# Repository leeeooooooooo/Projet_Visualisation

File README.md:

ce dossier contient l’api flask permettant de gérer les échanges entre la base de données et l’interface web, incluant l’authentification, la récupération des consommations et la gestion des seuils.

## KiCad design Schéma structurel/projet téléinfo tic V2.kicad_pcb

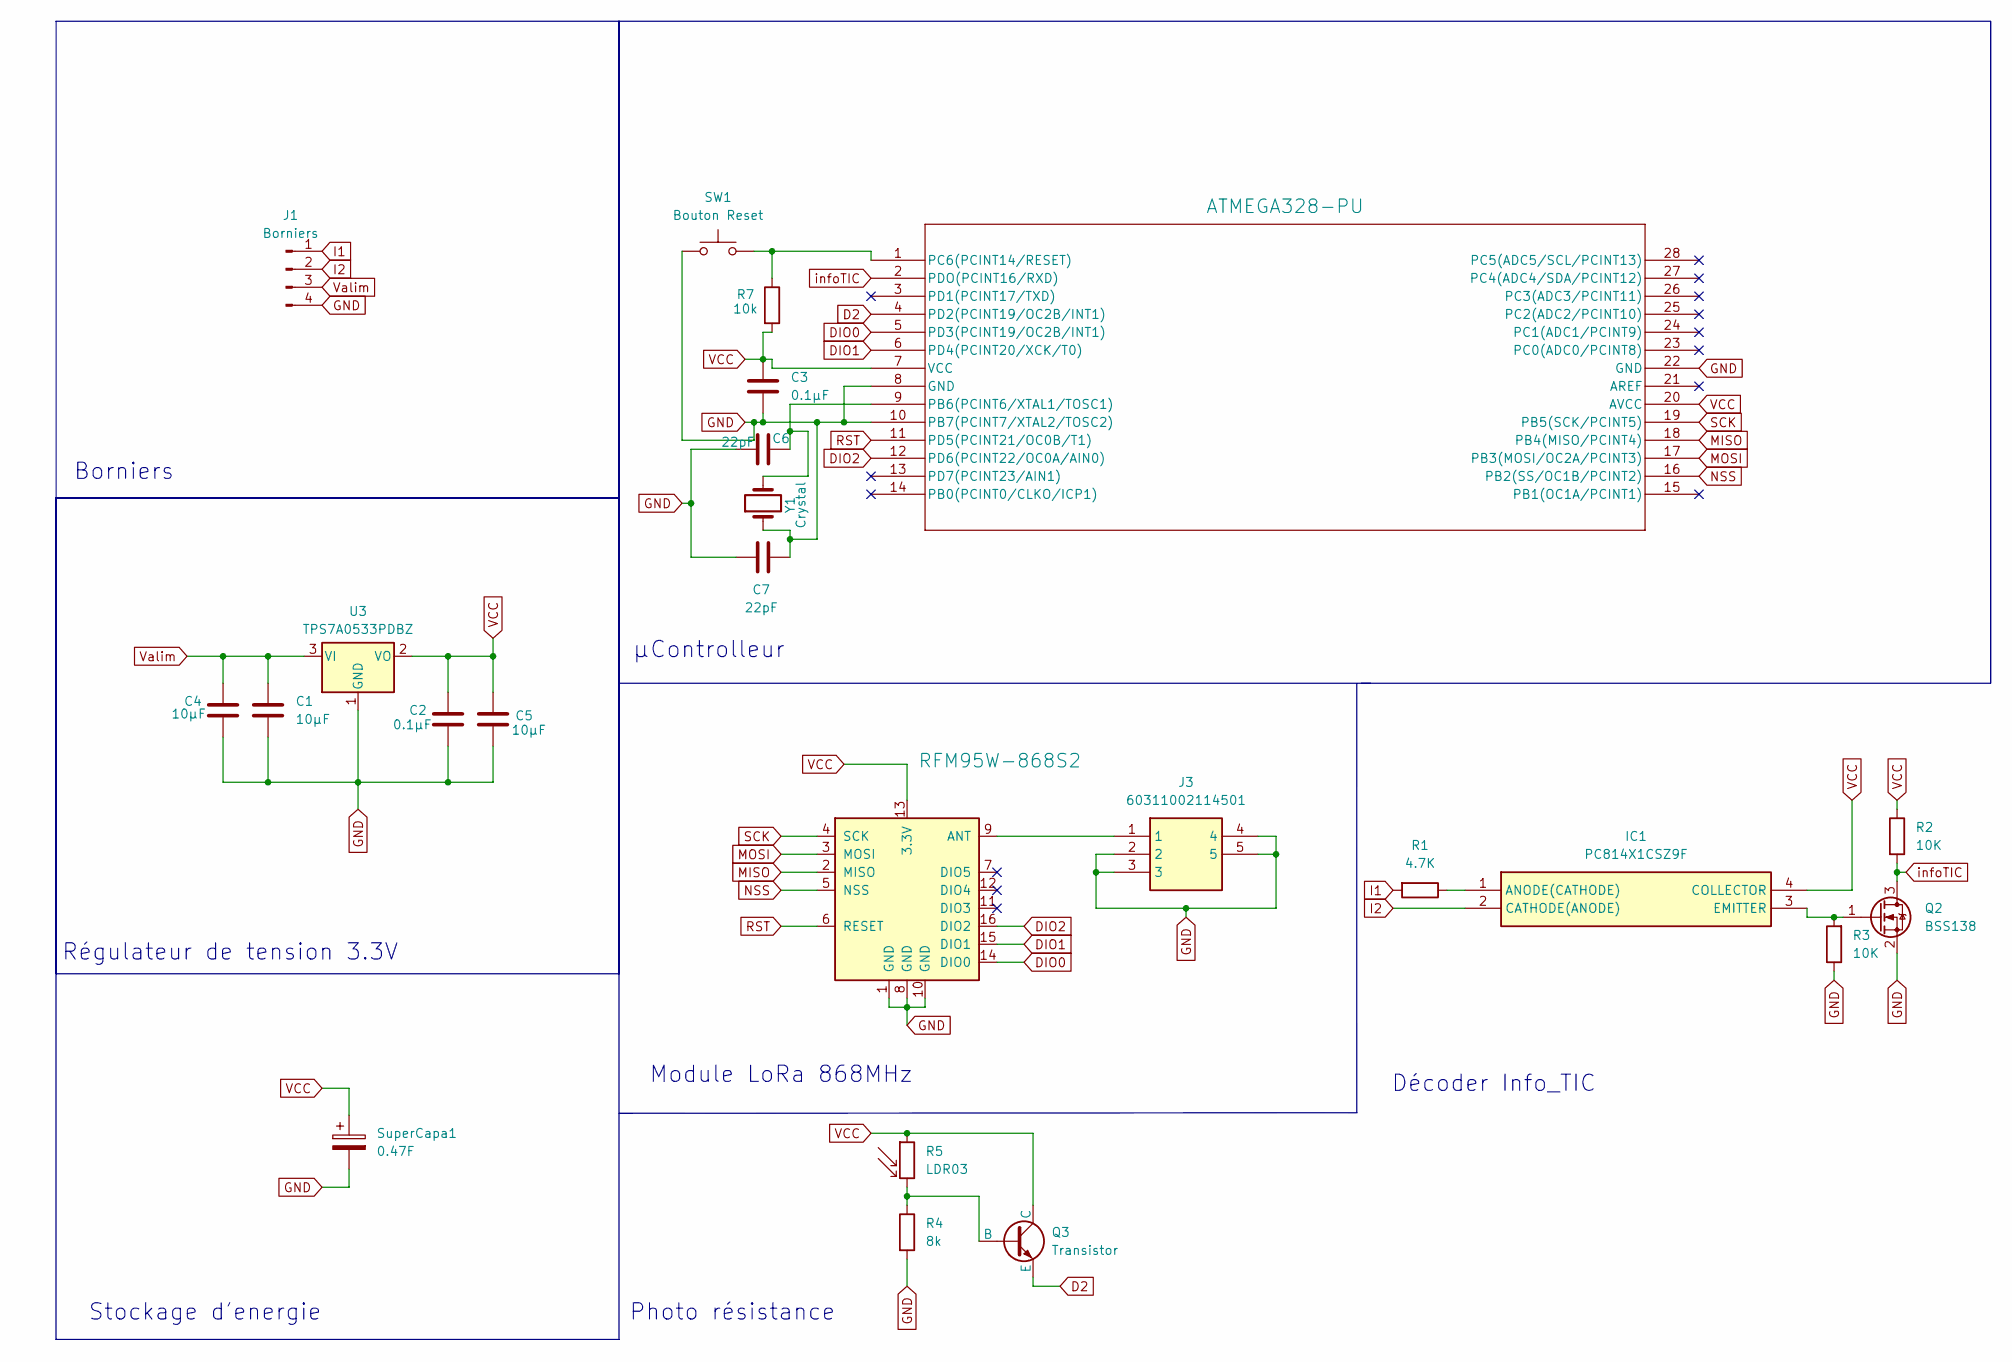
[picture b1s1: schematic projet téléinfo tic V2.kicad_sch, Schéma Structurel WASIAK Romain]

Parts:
C1, C4, C5: 10µF; CAPC3216X180N
C2, C3: 0.1µF; CAPC3216X180N
C6, C7: 22pF; CAPC3216X180N
IC1: PC814X1CSZ9F; DIP762W60P254L460H450Q4N; Manufacturer_Part_Number PC814X1CSZ9F; Mouser Part Number 852-PC814X1CSZ9F
J1: Borniers; 7966834
J3: 60311002114501; Manufacturer_Part_Number 60311002114501; Mouser Part Number 710-60311002114501
Q2: BSS138; SOT95P240X120-3N
Q3: Transistor; 2N2222A
R1: 4.7K; RESC3116X70N
R2, R3: 10K; RESC3216X74N
R4: 8k; ERJ8ENF1000V
R5: LDR03; PDVP8103
R7: 10k; RESC3216X74N
SW1: Bouton Reset; B3FS1012P
SuperCapa1: 0.47F; SCMQ14C474MRBA0
U2: RFM95W-868S2; XCVR_RFM95W-868S2
U3: TPS7A0533PDBZ; SOT95P237X112-3N
U4: ATMEGA328-PU; DIP1016W53P254L3468H457Q28N
Y1: Crystal; 830055663

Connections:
D2: Q3.3 (E), U4.4 (PD2(PCINT19/OC2B/INT1))
DIO0: U2.14 (DIO0), U4.5 (PD3(PCINT19/OC2B/INT1))
DIO1: U2.15 (DIO1), U4.6 (PD4(PCINT20/XCK/T0))
DIO2: U2.16 (DIO2), U4.12 (PD6(PCINT22/OC0A/AIN0))
GND: C1.2, C2.2, C3.2, C4.2, C5.2, C6.1, C7.1, C7.2, J1.4, J3.2, J3.3, J3.4, J3.5, Q2.2 (S), R3.1, R4.2, SW1.1, SuperCapa1.2, U2.1 (GND), U2.8 (GND), U2.10 (GND), U3.1 (GND), U4.8 (GND), U4.10 (PB7(PCINT7/XTAL2/TOSC2)), U4.22 (GND), Y1.1
I1: J1.1, R1.2
I2: IC1.2 (CATHODE(ANODE)), J1.2
MISO: U2.2 (MISO), U4.18 (PB4(MISO/PCINT4))
MOSI: U2.3 (MOSI), U4.17 (PB3(MOSI/OC2A/PCINT3))
NSS: U2.5 (NSS), U4.16 (PB2(SS/OC1B/PCINT2))
unnamed: IC1.1 (ANODE(CATHODE)), R1.1
unnamed: IC1.3 (EMITTER), Q2.1 (G), R3.2
unnamed: Q3.2 (B), R4.1, R5.2
unnamed: J3.1, U2.9 (ANT)
unnamed: C6.2, U4.9 (PB6(PCINT6/XTAL1/TOSC1)), Y1.2
unnamed: R7.1, SW1.2, U4.1 (PC6(PCINT14/RESET))
RST: U2.6 (RESET), U4.11 (PD5(PCINT21/OC0B/T1))
SCK: U2.4 (SCK), U4.19 (PB5(SCK/PCINT5))
VCC: C2.1, C3.1, C5.1, IC1.4 (COLLECTOR), Q3.1 (C), R2.1, R5.1, R7.2, SuperCapa1.1, U2.13 (3.3V), U3.2 (VO), U4.7 (VCC), U4.20 (AVCC)
Valim: C1.1, C4.1, J1.3, U3.3 (VI)
infoTIC: Q2.3 (D), R2.2, U4.2 (PDO(PCINT16/RXD))

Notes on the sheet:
Stockage d'energie
µControlleur
Décoder Info_TIC
Borniers
Module LoRa 868MHz
Régulateur de tension 3.3V
Photo résistance

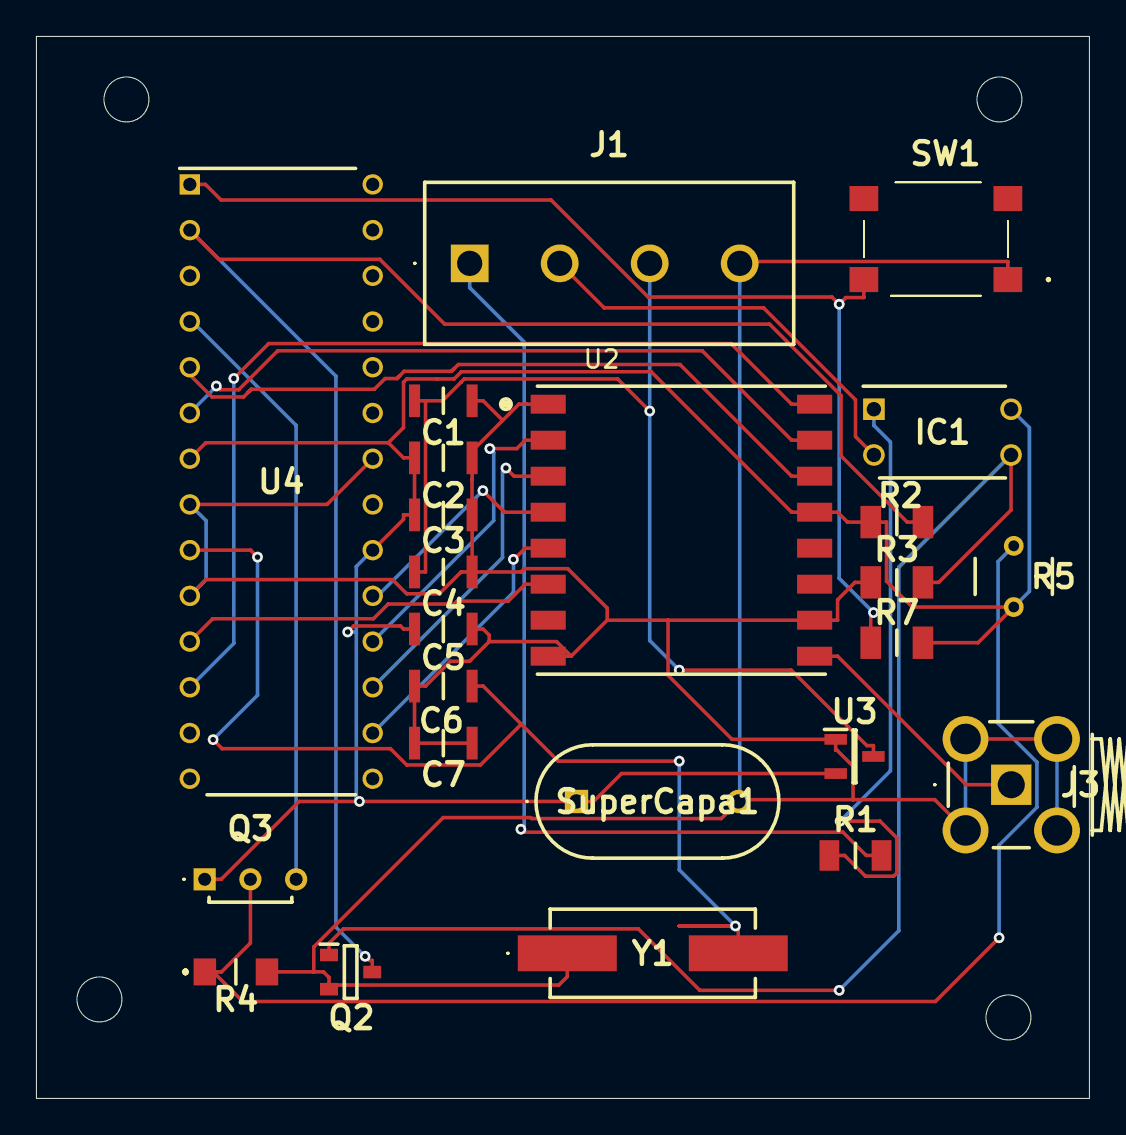
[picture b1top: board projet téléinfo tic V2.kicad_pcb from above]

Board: 2 copper layers, 58.5 x 59.0 mm, 24 parts (0 on the bottom side), 21 nets.

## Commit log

2025-03-04 Ajouté(e) Diagramme sans nom.drawio
2025-03-04 Mettre à jour Diagramme sans nom.drawio
2025-03-10 réseau
2025-04-25 Ajouté(e) synoptique.drawio
2025-04-25 Mettre à jour synoptique.drawio
2025-04-25 Ajouté(e) Synoptique_Réel.drawio
2025-04-25 Mettre à jour Synoptique_Réel.drawio
2025-04-25 Ajouté(e) Diagramme_déploiement.drawio
2025-04-25 Mettre à jour Diagramme_déploiement.drawio
2025-04-25 Ajouté(e) Diagramme_Classe_Frontend.drawio
2025-04-25 Mettre à jour Diagramme_Classe_Frontend.drawio
2025-04-29 Premier commit de mon projet
2025-05-05 Connexion session payload visible / configuration gérant campeur ok
2025-05-05 Ajout de la page connexion.vue avec session pas sécurisé
2025-05-06 Ajouté(e) Schema_reseau.drawio
2025-05-06 Mettre à jour Schema_reseau.drawio
2025-05-22 page configuration matin/midi/soir/nuit fonctionnelle
2025-05-23 page connexion avec emplacement fonctionnelle
2025-05-26 Commit serveur nginx et site en https
2025-06-02 Connexion session probleme sur panneau, config en https
2025-06-03 Code panneau qui fonctionne
2025-06-03 Commit pour dossier
2025-06-04 Create MCD_Global
2025-06-04 Rename mcd_2.png to mcd_2eme_essai.png
2025-06-04 Rename mcd_2eme_essai.png to mcd_final.png
2025-06-04 Rename mcdfinal.png to mcd_2eme.png
2025-06-04 Rename mcdtest.png to mcd_debut.png
2025-06-04 Rename mcd_depart.png to mcd_2eme.png
2025-06-04 Rename mcd_2.png to mcd_final.png
2025-06-04 Commit entier
2025-06-04 Déplacement des fichiers de configuration et README vers Frontend-codes
2025-06-04 Déplacement des dossiers bouchonnage et certificats vers Frontend-docs
2025-06-04 Déplacement de Mode_Emploi.docx dans Frontend-docs
2025-06-04 Déplacement des fichiers .browserslistrc et .gitignore dans Frontend-codes
2025-06-04 Rename test uni modifer_seuils.png to test_modifer_seuils.png
2025-06-04 Rename Frontend-docs/certificats/selfsigned.crt to Frontend-codes/certificatsselfsigned.crt
2025-06-04 changement de place
2025-06-04 Rename Frontend-codes/certificatsselfsigned.crt to Frontend-codes/certificats/certificatsselfsigned.crt
2025-06-04 Rename diag classe.png to diagramme_class.png
2025-06-05 Commit du code API/MQTT
2025-06-05 Rename mqtt.py to MQTT-code
2025-06-05 Rename MQTT-code to MQTT/MQTT-codes
2025-06-05 Rename MQTT/MQTT-codes to MQTT-codes
2025-06-05 Rename app.py to API/app.py
2025-06-05 Rename cert.pem to API/cert.pem
2025-06-05 Rename app.log to API/app.log
2025-06-05 Rename .env to API/.env
2025-06-05 Rename key.pem to API/key.pem
2025-06-05 Rename pyvenv.cfg to API/pyvenv.cfg
